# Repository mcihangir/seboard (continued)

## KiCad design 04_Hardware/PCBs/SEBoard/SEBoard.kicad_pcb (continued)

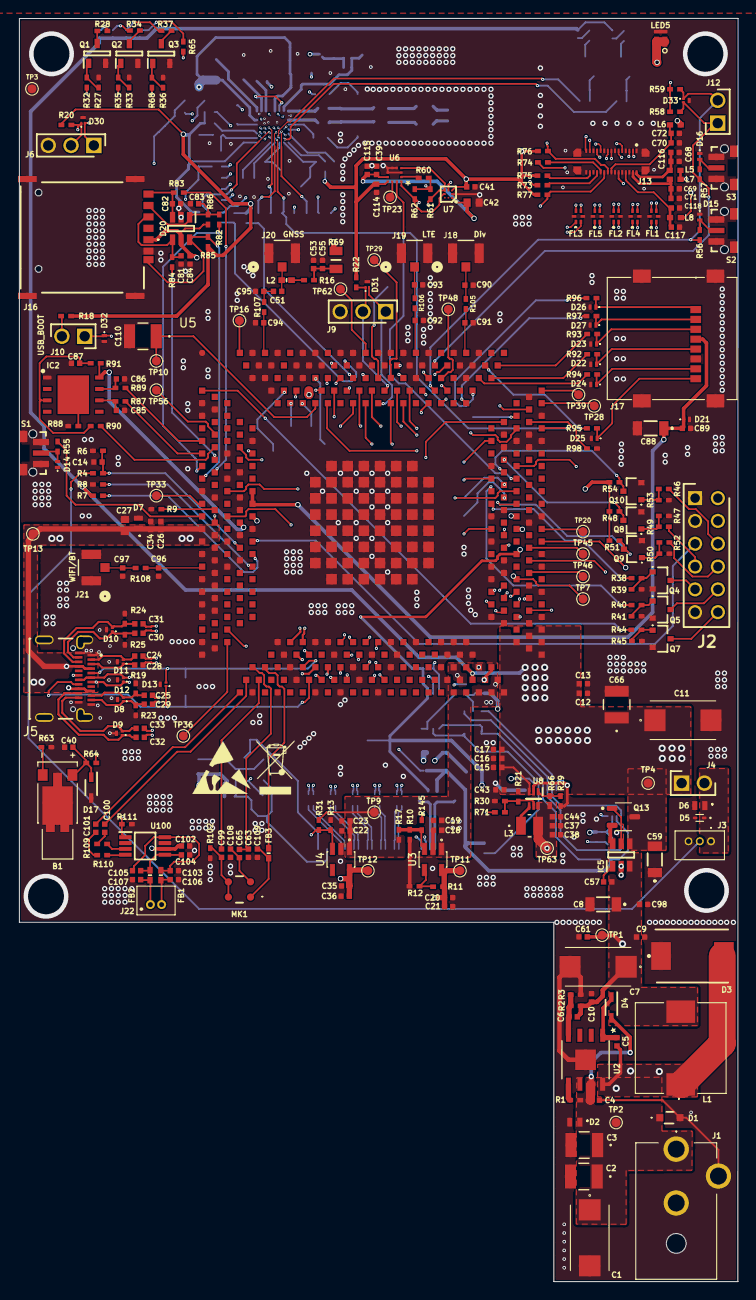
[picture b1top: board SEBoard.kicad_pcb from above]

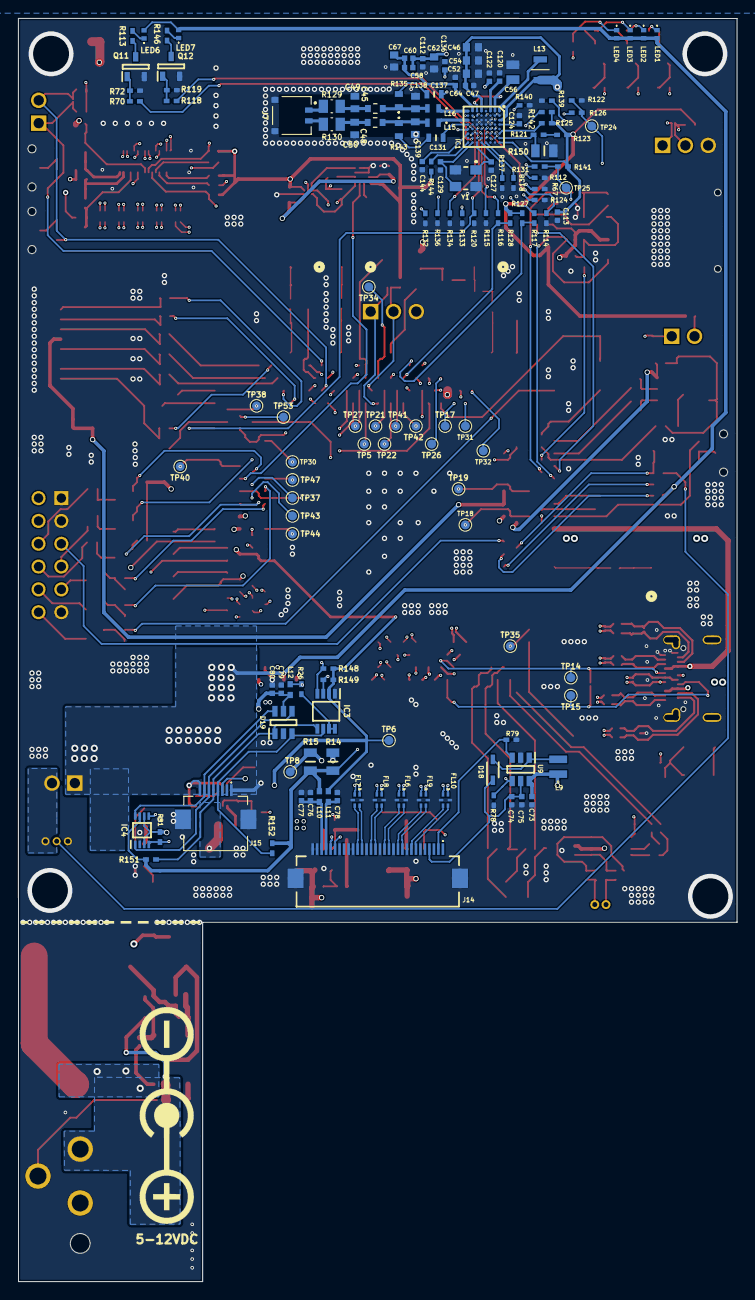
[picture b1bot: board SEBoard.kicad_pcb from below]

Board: 6 copper layers, 80.0 x 140.6 mm, 439 parts (141 on the bottom side), 329 nets.

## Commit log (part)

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2026-04-24 feat: initial working version
2026-04-24 feat: Added SE250B4 symbol and footprint, refactor symbol into functional units
2026-04-26 feat(schematic): add SE250B4 symbol to schematic (unchecked)
2026-04-28 feat: Updated schematic layout and moved new components to Layout
2026-04-29 feat: Updated schematic
